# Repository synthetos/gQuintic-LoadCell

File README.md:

# gQuintic-LoadCell
Load cell adapter for gQuintic motion controller board

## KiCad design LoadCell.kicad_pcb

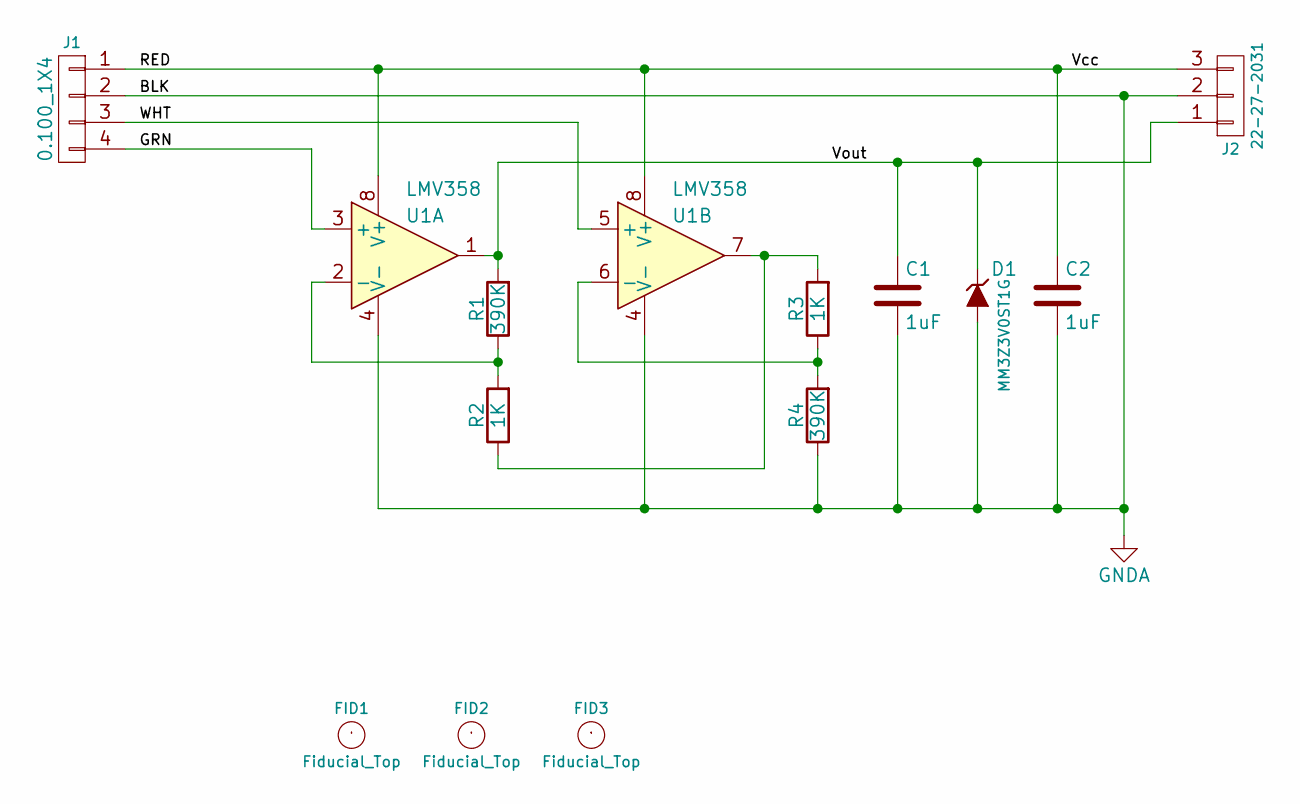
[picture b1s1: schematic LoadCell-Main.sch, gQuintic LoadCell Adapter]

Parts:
C1, C2: 1uF; C_0402
D1: MM3Z3V0ST1G; D_SOD-323
FID1, FID2, FID3: Fiducial_Top; Fiducial_0.040_Top
J1: 0.100_1X4; Socket_Strip_Straight_1x04_Pitch2.00mm
J2: 22-27-2031; 0.100_1x3_small
R1, R4: 390K; R_0402
R2, R3: 1K; R_0402
U1: LMV358; MSOP-8_3x3mm_Pitch0.65mm

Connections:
/Main Sheet/GRN: J1.4, U1.3 (+)
/Main Sheet/RED: C2.1, J1.1, J2.3, U1.8 (V+)
/Main Sheet/Vout: C1.1, D1.1 (K), J2.1, R1.2, U1.1
/Main Sheet/WHT: J1.3, U1.5 (+)
GNDA: C1.2, C2.2, D1.2 (A), J1.2, J2.2, R4.1, U1.4 (V-)
unnamed: R1.1, R2.2, U1.2 (-)
unnamed: R2.1, R3.2, U1.7
unnamed: R3.1, R4.2, U1.6 (-)

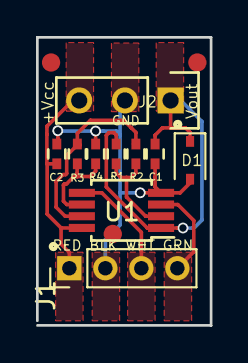
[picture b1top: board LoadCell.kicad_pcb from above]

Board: 2 copper layers, 9.7 x 16.0 mm, 13 parts (0 on the bottom side), 8 nets.

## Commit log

2018-05-04 Copied old files in from LoadCellAmplifier project
2018-05-04 First cut
2018-05-10 Generated revA output files
2018-05-10 Added zip file to gitignore
2018-06-21 Corrected miswiring
